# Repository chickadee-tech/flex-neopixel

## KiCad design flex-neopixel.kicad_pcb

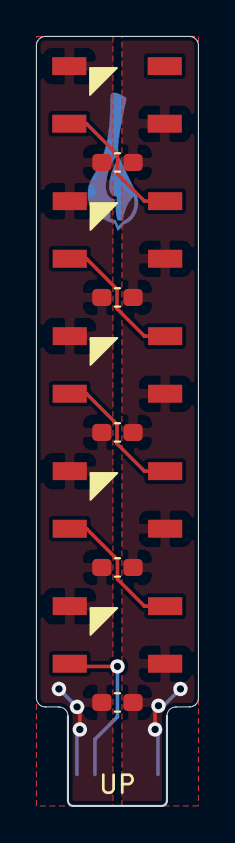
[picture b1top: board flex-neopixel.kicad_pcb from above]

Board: 2 copper layers, 8.9 x 42.7 mm, 11 parts (0 on the bottom side), 7 nets.

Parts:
C1, C2, C3, C4, C5: 0.1uF; C_0603_1608Metric_Pad1.08x0.95mm_HandSolder
D1, D2, D3, D4, D5: WS2812B; LED_WS2812B_PLCC4_5.0x5.0mm_P3.2mm_HandSolder
J1: 10POSFPC; 10pins-flex

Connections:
+3V3: C1.1, C2.1, C3.1, C4.1, C5.1, D1.1, D2.1, D3.1, D4.1, D5.1, J1.10
GND: C1.2, C2.2, C3.2, C4.2, C5.2, D1.3, D2.3, D3.3, D4.3, D5.3, J1.1
unnamed: D1.2, D5.4
unnamed: D1.4, D4.2
unnamed: D2.2, D4.4
unnamed: D2.4, D3.2
unnamed: D3.4, J1.3

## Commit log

2021-02-15 5 neopixels
